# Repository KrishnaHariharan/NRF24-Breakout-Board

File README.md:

# NRF24-Breakout-Board
This Project is about designing of a breakout board  PCB module for NRF24 using KICAD
Here I have created my own schematic and symbol for a nrf24 and added footprints to it. This breakout board will help nrf24 to be directly interfaced with arduino without any breadboard inbetwee.

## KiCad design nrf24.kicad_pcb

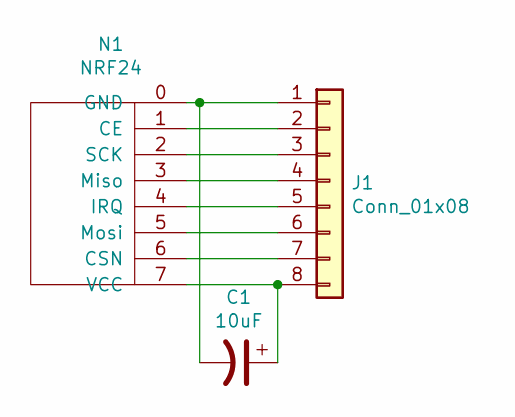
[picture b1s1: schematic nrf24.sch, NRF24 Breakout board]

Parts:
C1: 10uF; CP_Radial_D10.0mm_P5.00mm
J1: Conn_01x08; PinHeader_1x08_P2.54mm_Horizontal
N1: NRF24; nRF24

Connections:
unnamed: C1.1, J1.8, N1.7 (VCC)
unnamed: C1.2, J1.1, N1.0 (GND)
unnamed: J1.2, N1.1 (CE)
unnamed: J1.3, N1.2 (SCK)
unnamed: J1.4, N1.3 (Miso)
unnamed: J1.5, N1.4 (IRQ)
unnamed: J1.6, N1.5 (Mosi)
unnamed: J1.7, N1.6 (CSN)

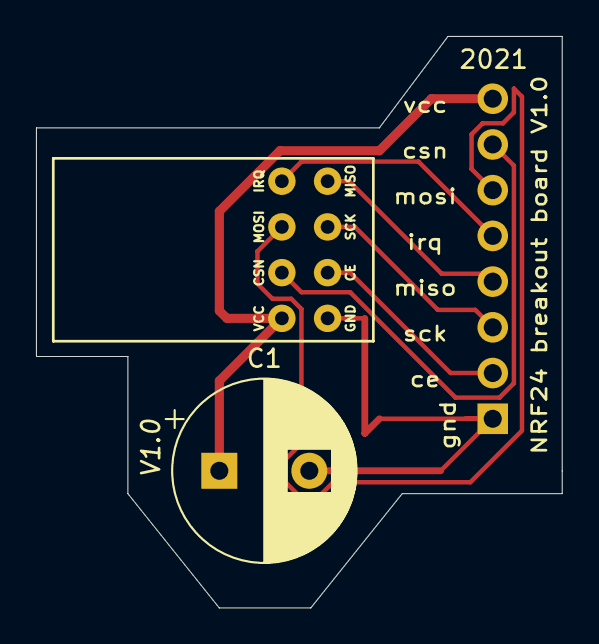
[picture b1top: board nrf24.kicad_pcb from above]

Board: 2 copper layers, 29.2 x 31.8 mm, 3 parts (1 on the bottom side), 8 nets.

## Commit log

2021-10-25 Add files via upload
    Gerber Files are also included here.
